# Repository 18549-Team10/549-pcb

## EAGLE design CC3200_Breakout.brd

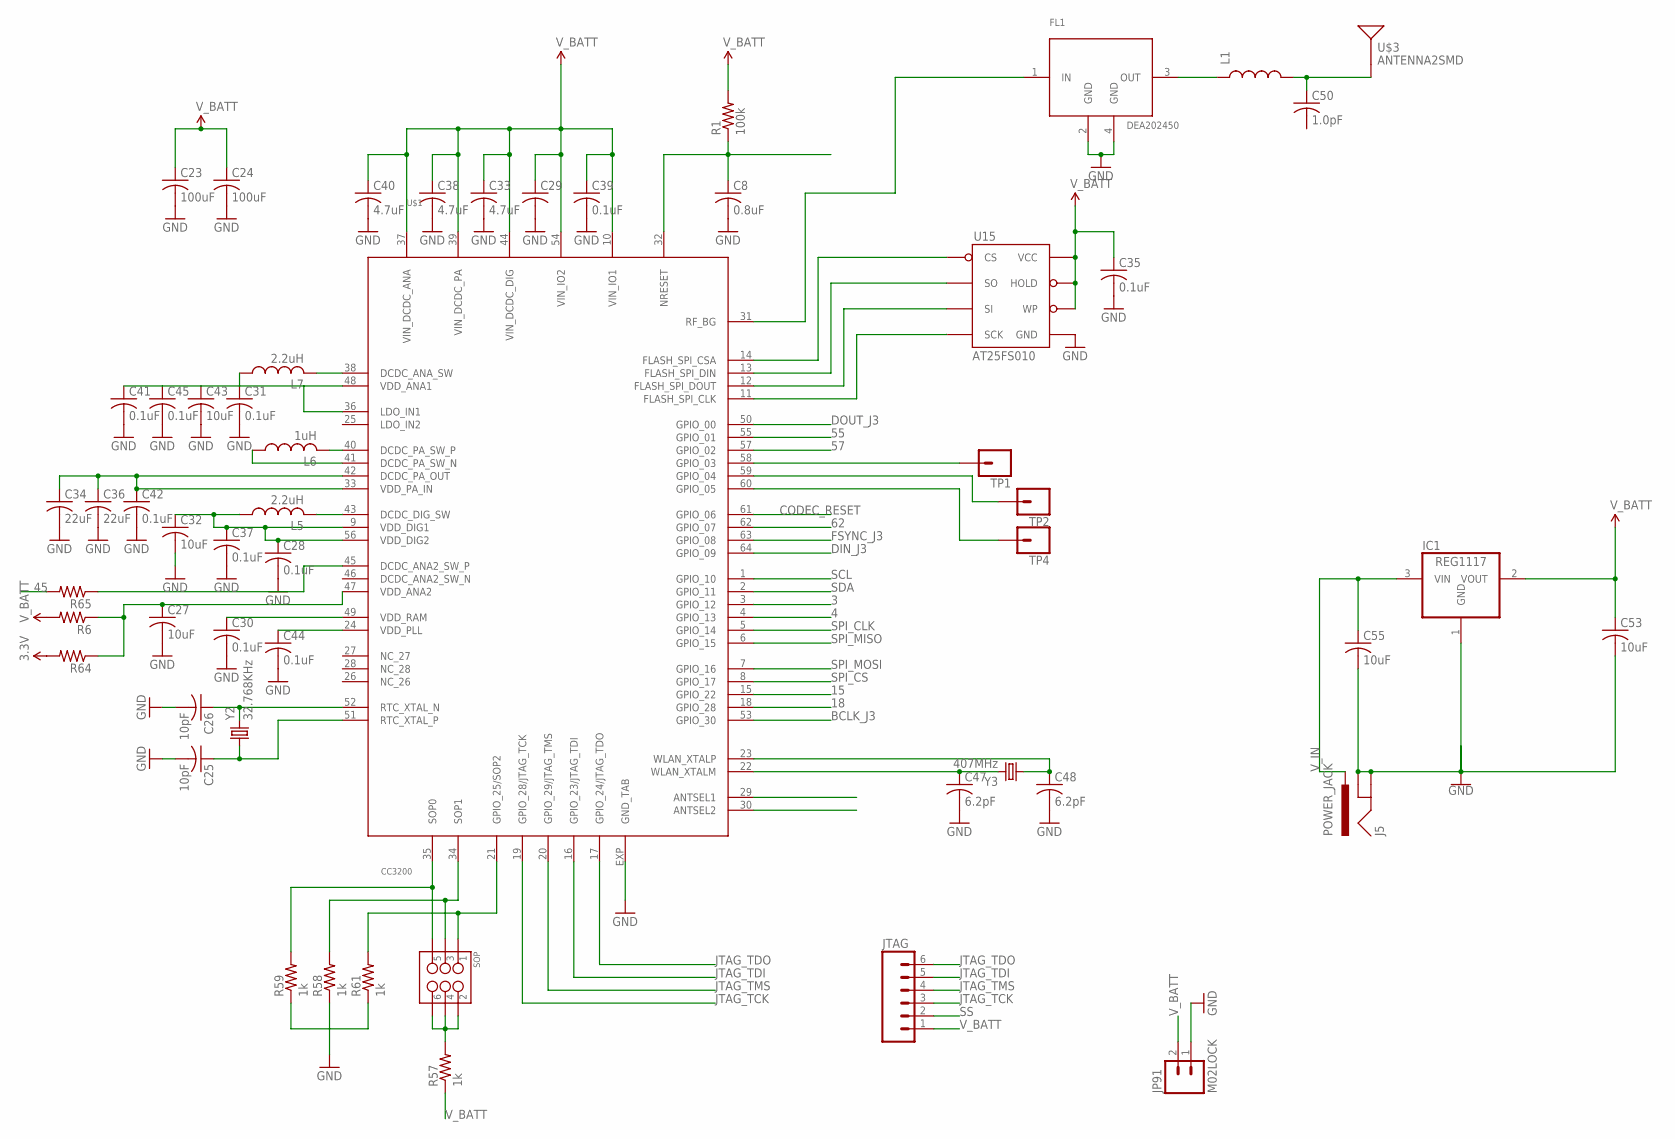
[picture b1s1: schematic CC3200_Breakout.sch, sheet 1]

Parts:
C8: 0.8uF; C0402K
C23, C24: 100uF; C0402K
C25, C26: 10pF; C0402K
C27, C32, C43: 10uF; C0402K
C28, C30, C31, C35, C37, C39, C41, C42, C44, C45: 0.1uF; C0402K
C29: C-USC0402K; C0402K
C33, C38, C40: 4.7uF; C0402K
C34, C36: 22uF; C0402K
C47, C48: 6.2pF; C0402K
C50: 1.0pF; C0402K
C53, C55: 10uF; C1206
FL1: DEA202450
IC1: REG1117; SOT223
J5: POWER_JACK; POWER_JACK_PTH
JP91: M02LOCK; 1X02_LOCK
JTAG: M06SILK_FEMALE_PTH; 1X06
L1: INDUCTOR-SPARKFUN0402; C0402
L5, L7: 2.2uH; L2012C
L6: 1uH; L2012C
R1: 100k; R0402
R6, R64, R65: R-US_R0402; R0402
R57, R58, R59, R61: 1k; R0402
SOP: M03X22X3_SILK_MALE_PTH; 2X3
TP1, TP2, TP4: CONN_01; 1X01
U15: AT25FS010; SO08WIDE
U$1: CC3200; PVQFN-N64
U$3: ANTENNA2SMD; ANTENNA-CHIP2
Y2: 32.768KHz; CRYSTAL-SMD-5X3
Y3: 407MHz; CRYSTAL-SMD-5X3

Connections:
3: U$1.3 (GPIO_12)
3.3V: R64.2
4: U$1.4 (GPIO_13)
15: U$1.15 (GPIO_22)
18: U$1.18 (GPIO_28)
45: R65.2
55: U$1.55 (GPIO_01)
57: U$1.57 (GPIO_02)
58: TP1.1, U$1.58 (GPIO_03)
59: TP2.1, U$1.59 (GPIO_04)
60: TP4.1, U$1.60 (GPIO_05)
62: U$1.62 (GPIO_07)
BCLK_J3: U$1.53 (GPIO_30); also elsewhere on the board
CODEC_RESET: U$1.61 (GPIO_06); also elsewhere on the board
DIN_J3: U$1.64 (GPIO_09); also elsewhere on the board
DOUT_J3: U$1.50 (GPIO_00); also elsewhere on the board
FSYNC_J3: U$1.63 (GPIO_08); also elsewhere on the board
JTAG_TCK: JTAG.3, U$1.19 (GPIO_28/JTAG_TCK)
JTAG_TDI: JTAG.5, U$1.16 (GPIO_23/JTAG_TDI)
JTAG_TDO: JTAG.6, U$1.17 (GPIO_24/JTAG_TDO)
JTAG_TMS: JTAG.4, U$1.20 (GPIO_29/JTAG_TMS)
unnamed: C26.1, U$1.52 (RTC_XTAL_N), Y2.3 (2)
unnamed: C25.1, U$1.51 (RTC_XTAL_P), Y2.1
unnamed: C31.1, C41.1, C43.1, C45.1, L7.1, U$1.36 (LDO_IN1), U$1.48 (VDD_ANA1)
unnamed: L7.2, U$1.38 (DCDC_ANA_SW)
unnamed: R57.2, SOP.2, SOP.4, SOP.6
unnamed: L6.2, U$1.40 (DCDC_PA_SW_P)
unnamed: L6.1, U$1.41 (DCDC_PA_SW_N)
unnamed: FL1.1 (IN), U$1.31 (RF_BG)
unnamed: C34.1, C36.1, C42.1, U$1.33 (VDD_PA_IN), U$1.42 (DCDC_PA_OUT)
unnamed: L5.2, U$1.43 (DCDC_DIG_SW)
unnamed: R65.1, U$1.45 (DCDC_ANA2_SW_P)
unnamed: R59.2, SOP.5, U$1.35 (SOP0)
unnamed: C8.1, R1.1, U$1.32 (NRESET)
unnamed: C28.1, C32.1, C37.1, L5.1, U$1.9 (VDD_DIG1), U$1.56 (VDD_DIG2)
unnamed: C30.1, U$1.49 (VDD_RAM)
unnamed: C44.1, U$1.24 (VDD_PLL)
unnamed: C27.1, R6.1, R64.1, U$1.47 (VDD_ANA2)
unnamed: R58.2, SOP.3, U$1.34 (SOP1)
unnamed: R61.2, SOP.1, U$1.21 (GPIO_25/SOP2)
unnamed: C47.1, U$1.22 (WLAN_XTALM), Y3.3 (2)
unnamed: C48.1, U$1.23 (WLAN_XTALP), Y3.1
unnamed: U15.1 (CS), U$1.14 (FLASH_SPI_CSA)
unnamed: U15.2 (SO), U$1.13 (FLASH_SPI_DIN)
unnamed: U15.5 (SI), U$1.12 (FLASH_SPI_DOUT)
unnamed: U15.6 (SCK), U$1.11 (FLASH_SPI_CLK)
unnamed: FL1.3 (OUT), L1.1
SCL: U$1.1 (GPIO_10); also elsewhere on the board
SDA: U$1.2 (GPIO_11); also elsewhere on the board
SPI_CLK: U$1.5 (GPIO_14)
SPI_CS: U$1.8 (GPIO_17)
SPI_MISO: U$1.6 (GPIO_15)
SPI_MOSI: U$1.7 (GPIO_16)
SS: C8.2, C23.2, C24.2, C25.2, C26.2, C27.2, C28.2, C29.2, C30.2, C31.2, C32.2, C33.2, C34.2, C35.2, C36.2, C37.2, C38.2, C39.2, C40.2, C41.2, C42.2, C43.2, C44.2, C45.2, C47.2, C48.2, C50.1, C53.2, C55.2, FL1.2 (GND), FL1.4 (GND), IC1.1 (GND), J5.GND, J5.GNDBREAK, JP91.1, JTAG.2, L1.2, R58.1, R59.1, R61.1, U15.4 (GND), U$1.EXP (GND_TAB), U$3.FEED; also elsewhere on the board
V_BATT: C23.1, C24.1, C29.1, C33.1, C35.1, C38.1, C39.1, C40.1, C53.1, IC1.2 (VOUT), JP91.2, JTAG.1, R1.2, R6.2, R57.1, U15.3 (WP), U15.7 (HOLD), U15.8 (VCC), U$1.10 (VIN_IO1), U$1.37 (VIN_DCDC_ANA), U$1.39 (VIN_DCDC_PA), U$1.44 (VIN_DCDC_DIG), U$1.54 (VIN_IO2)
V_IN: C55.1, IC1.3 (VIN), J5.PWR

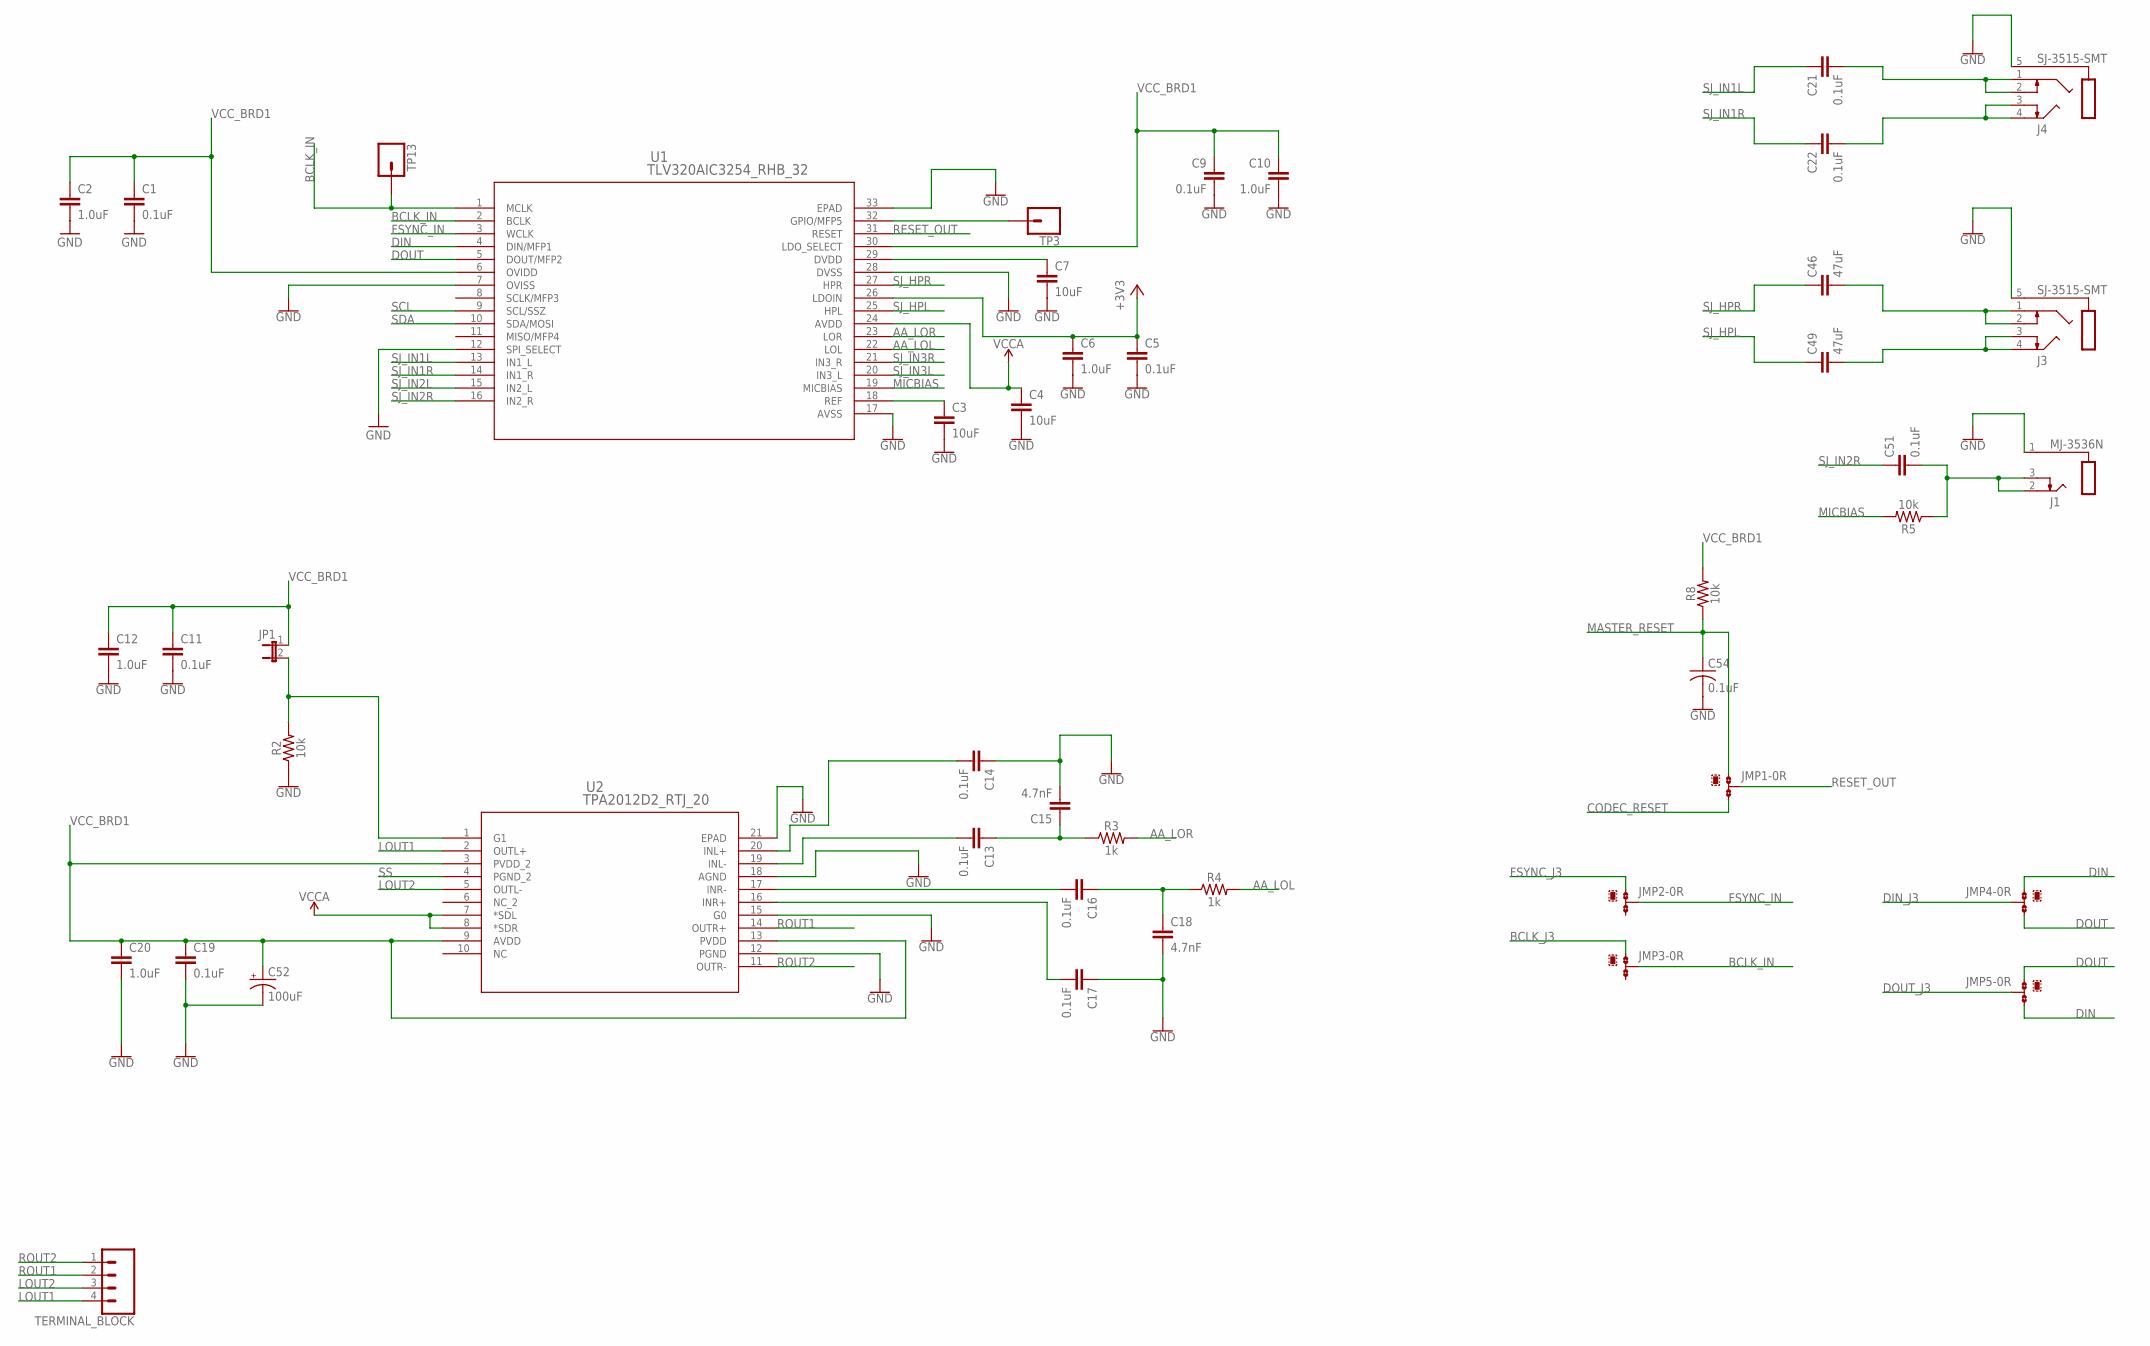
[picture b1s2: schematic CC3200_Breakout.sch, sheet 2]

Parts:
C1, C5, C9, C11, C13, C14, C16, C17, C19, C21, C22, C51: 0.1uF; 0402
C2, C6, C10, C12, C20: 1.0uF; 0402
C3, C4, C7: 10uF; 0603
C15, C18: 4.7nF; 0603
C46, C49: 47uF; 0603
C52: 100uF; PANASONIC_D
C54: 0.1uF; C0402K
J1: MJ-3536N
J3, J4: SJ-3515-SMT
JMP1, JMP2, JMP3, JMP4, JMP5: 0R-JUMPA; A0R-JMP
JP1: JUMPER-2PTH; 1X02
R2, R5, R8: 10k; 0603
R3, R4: 1k; 0603
TERMINAL_BLOCK: CONN_04JST-PTH; JST-4-PTH
TP3, TP13: CONN_01; 1X01
U1: TLV320AIC3254_RHB_32; RHB32_3P45X3P45
U2: TPA2012D2_RTJ_20; RTJ20_2P7X2P7

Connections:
+3V3: C5.1, C6.1, U1.26 (LDOIN)
AA_LOL: R4.2, U1.22 (LOL)
AA_LOR: R3.2, U1.23 (LOR)
BCLK_IN: JMP3.2, TP13.1, U1.1 (MCLK), U1.2 (BCLK)
BCLK_J3: JMP3.1; also elsewhere on the board
CODEC_RESET: JMP1.3; also elsewhere on the board
DIN: JMP4.1, JMP5.3, U1.4 (DIN/MFP1)
DIN_J3: JMP4.2; also elsewhere on the board
DOUT: JMP4.3, JMP5.1, U1.5 (DOUT/MFP2)
DOUT_J3: JMP5.2; also elsewhere on the board
FSYNC_IN: JMP2.2, U1.3 (WCLK)
FSYNC_J3: JMP2.1; also elsewhere on the board
LOUT1: TERMINAL_BLOCK.4, U2.2 (OUTL+)
LOUT2: TERMINAL_BLOCK.3, U2.5 (OUTL-)
MASTER_RESET: C54.1, JMP1.1, R8.1
MICBIAS: R5.2, U1.19 (MICBIAS)
unnamed: C3.1, U1.18 (REF)
unnamed: TP3.1, U1.32 (GPIO/MFP5)
unnamed: JP1.2, R2.2, U2.1 (G1)
unnamed: C7.1, U1.29 (DVDD)
unnamed: C22.2, J4.3 (TS), J4.4 (T)
unnamed: C14.2, U2.20 (INL+)
unnamed: C13.1, C15.1, R3.1
unnamed: C13.2, U2.19 (INL-)
unnamed: C16.2, U2.17 (INR-)
unnamed: C16.1, C18.1, R4.1
unnamed: C17.2, U2.16 (INR+)
unnamed: C21.2, J4.1 (R), J4.2 (RS)
unnamed: C46.2, J3.1 (R), J3.2 (RS)
unnamed: C49.2, J3.3 (TS), J3.4 (T)
unnamed: C51.2, J1.2 (T), J1.3 (TS), R5.1
RESET_OUT: JMP1.2, U1.31 (RESET)
ROUT1: TERMINAL_BLOCK.2, U2.14 (OUTR+)
ROUT2: TERMINAL_BLOCK.1, U2.11 (OUTR-)
SCL: U1.9 (SCL/SSZ); also elsewhere on the board
SDA: U1.10 (SDA/MOSI); also elsewhere on the board
SJ_HPL: C49.1, U1.25 (HPL)
SJ_HPR: C46.1, U1.27 (HPR)
SJ_IN1L: C21.1, U1.13 (IN1_L)
SJ_IN1R: C22.1, U1.14 (IN1_R)
SJ_IN2L: U1.15 (IN2_L)
SJ_IN2R: C51.1, U1.16 (IN2_R)
SJ_IN3L: U1.20 (IN3_L)
SJ_IN3R: U1.21 (IN3_R)
SS: C1.2, C2.2, C3.2, C4.2, C5.2, C6.2, C7.2, C9.2, C10.2, C11.2, C12.2, C14.1, C15.2, C17.1, C18.2, C19.2, C20.2, C52.-, C54.2, J1.1 (S), J3.5 (S), J4.5 (S), R2.1, U1.7 (OVISS), U1.12 (SPI_SELECT), U1.17 (AVSS), U1.28 (DVSS), U1.33 (EPAD), U2.4 (PGND_2), U2.12 (PGND), U2.15 (G0), U2.18 (AGND), U2.21 (EPAD); also elsewhere on the board
VCCA: C4.1, U1.24 (AVDD), U2.7 (*SDL), U2.8 (*SDR)
VCC_BRD1: C1.1, C2.1, C9.1, C10.1, C11.1, C12.1, C19.1, C20.1, C52.+, JP1.1, R8.2, U1.6 (OVIDD), U1.30 (LDO_SELECT), U2.3 (PVDD_2), U2.9 (AVDD), U2.13 (PVDD)

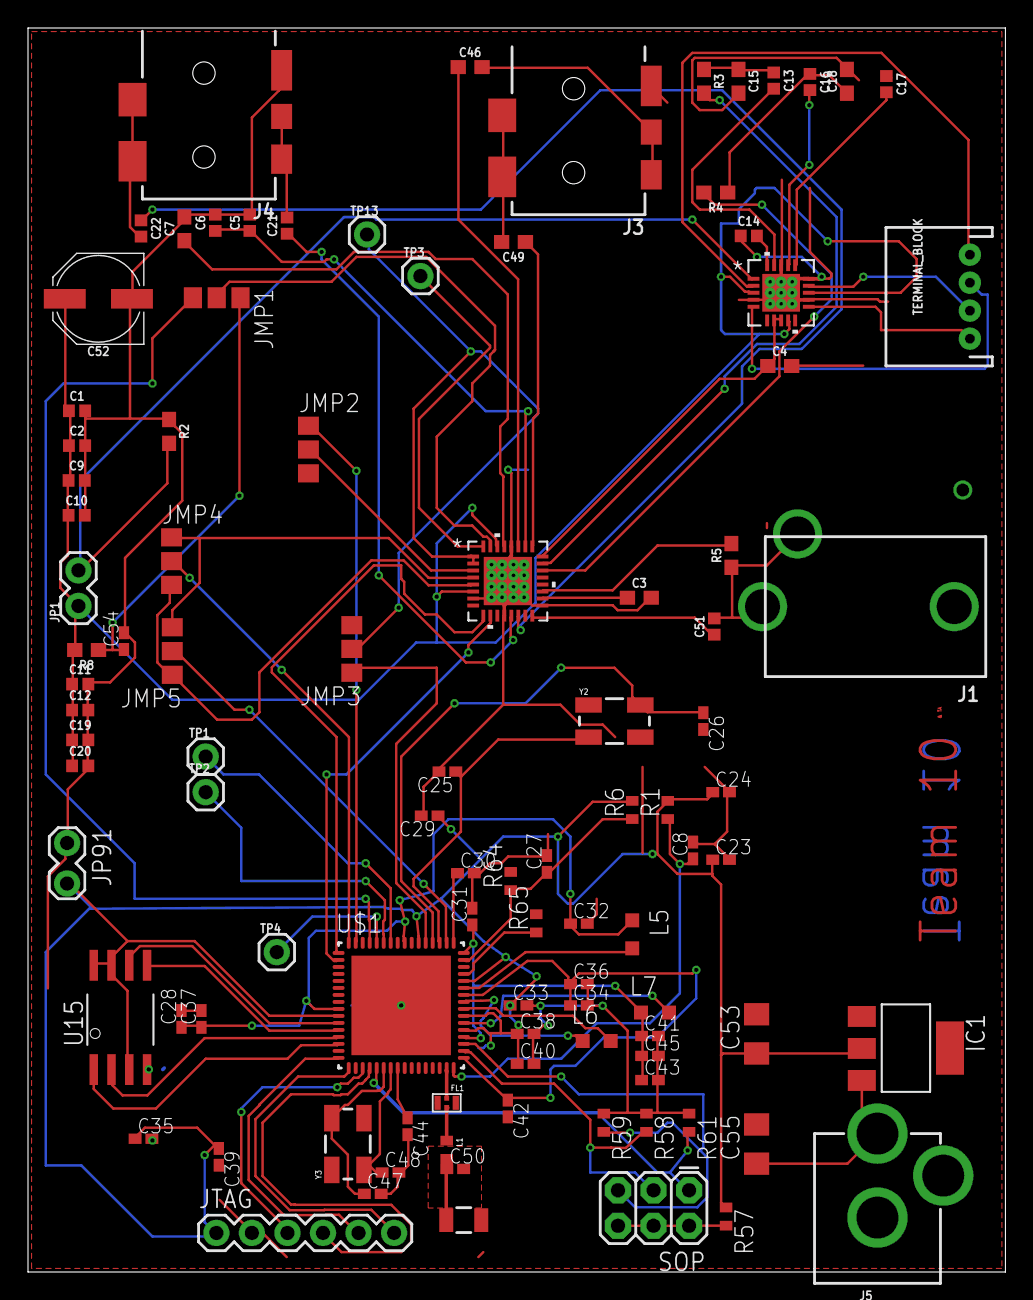
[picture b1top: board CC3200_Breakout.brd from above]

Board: 4 copper layers, 69.8 x 88.9 mm, 100 parts (0 on the bottom side), 79 nets.

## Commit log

2017-03-26 Added folders for device footprints, reference designs, and datasheets
2017-04-12 Audioboost recreated; eliminating need for breakout pins
2017-04-12 ready for routing
2017-04-12 proper files added now, ready to finish routing
2017-04-17 routed
2017-04-19 routing finished, BOM added
2017-04-25 before ripup and change to two layers
2017-04-25 Finished routing and reduced to 2 layers.
2017-04-27 I get by with a little help from Artur

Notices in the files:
parts and their libraries:
SparkFun-DigitalIC: Licensing: CC v3.0 Share-Alike You are welcome to use this library for commercial purposes.
SparkFun-Capacitors: Licensing: Creative Commons ShareAlike 4.0 International - https://creativecommons.org/licenses/by-sa/4.0
con-cuistack: Copyright (C) 2008, Bob Starr
